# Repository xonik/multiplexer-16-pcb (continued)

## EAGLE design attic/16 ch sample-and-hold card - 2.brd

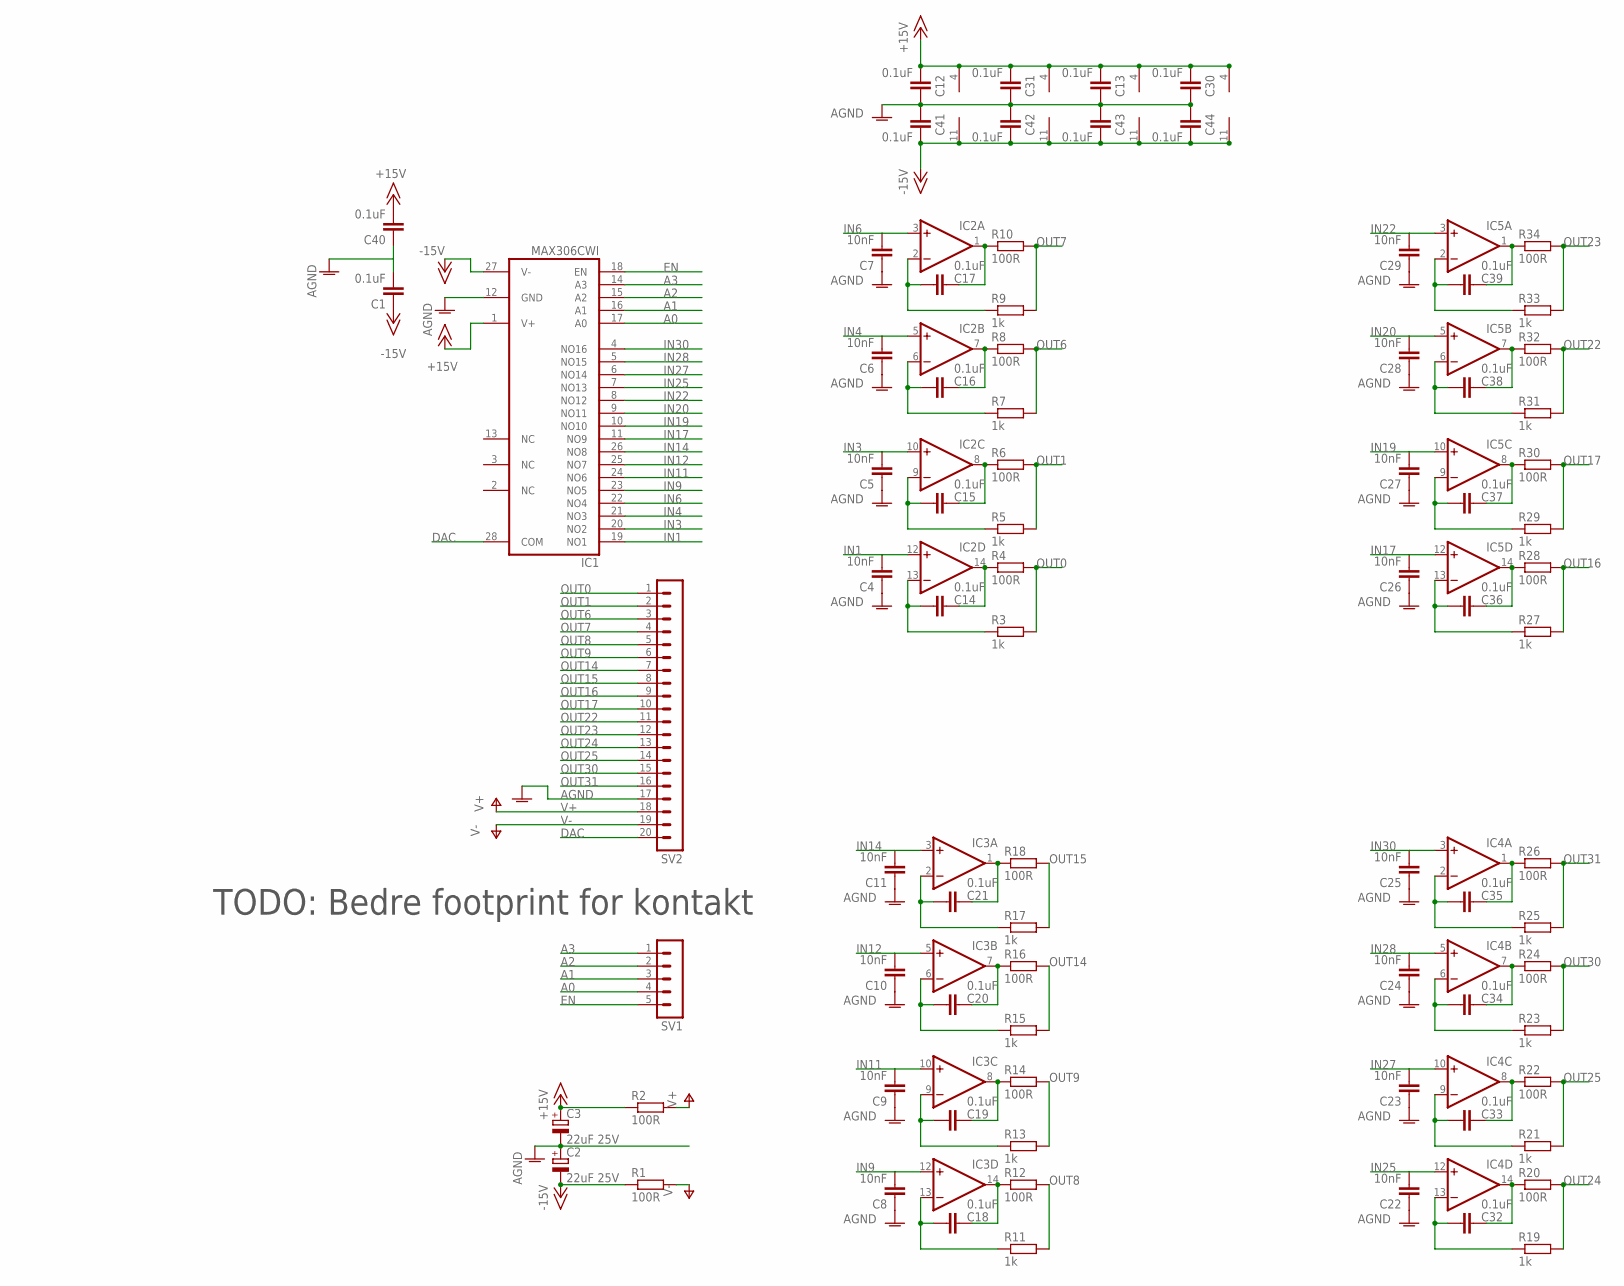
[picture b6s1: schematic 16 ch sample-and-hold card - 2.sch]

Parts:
C1, C12, C13, C14, C15, C16, C17, C18, C19, C20, C21, C30, C31, C32, C33, C34, C35, C36, C37, C38, C39, C40, C41, C42, C43, C44: 0.1uF; C0603
C2, C3: 22uF 25V; E2-5
C4, C5, C6, C7, C8, C9, C10, C11, C22, C23, C24, C25, C26, C27, C28, C29: 10nF; C1206
IC1: MAX306CWI; SO28L
IC2, IC3, IC4, IC5: TL074D; SO14
R1, R2: 100R; 0207/7
R3, R5, R7, R9, R11, R13, R15, R17, R19, R21, R23, R25, R27, R29, R31, R33: 1k; R0603
R4, R6, R8, R10, R12, R14, R16, R18, R20, R22, R24, R26, R28, R30, R32, R34: 100R; R0603
SV1: MA05-1
SV2: MA20-1

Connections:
+15V: C3.+, C12.1, C13.1, C30.1, C31.1, C40.2, IC1.1 (V+), IC2.4 (V+), IC3.4 (V+), IC4.4 (V+), IC5.4 (V+), R2.1
-15V: C1.1, C2.-, C41.2, C42.2, C43.2, C44.2, IC1.27 (V-), IC2.11 (V-), IC3.11 (V-), IC4.11 (V-), IC5.11 (V-), R1.1
A0: IC1.17 (A0), SV1.4
A1: IC1.16 (A1), SV1.3
A2: IC1.15 (A2), SV1.2
A3: IC1.14 (A3), SV1.1
AGND: C1.2, C2.+, C3.-, C4.1, C5.1, C6.1, C7.1, C8.1, C9.1, C10.1, C11.1, C12.2, C13.2, C22.1, C23.1, C24.1, C25.1, C26.1, C27.1, C28.1, C29.1, C30.2, C31.2, C40.1, C41.1, C42.1, C43.1, C44.1, IC1.12 (GND), SV2.17
DAC: IC1.28 (COM), SV2.20
EN: IC1.18 (EN), SV1.5
IN1: C4.2, IC1.19 (NO1), IC2.12 (+IN)
IN3: C5.2, IC1.20 (NO2), IC2.10 (+IN)
IN4: C6.2, IC1.21 (NO3), IC2.5 (+IN)
IN6: C7.2, IC1.22 (NO4), IC2.3 (+IN)
IN9: C8.2, IC1.23 (NO5), IC3.12 (+IN)
IN11: C9.2, IC1.24 (NO6), IC3.10 (+IN)
IN12: C10.2, IC1.25 (NO7), IC3.5 (+IN)
IN14: C11.2, IC1.26 (NO8), IC3.3 (+IN)
IN17: C26.2, IC1.11 (NO9), IC5.12 (+IN)
IN19: C27.2, IC1.10 (NO10), IC5.10 (+IN)
IN20: C28.2, IC1.9 (NO11), IC5.5 (+IN)
IN22: C29.2, IC1.8 (NO12), IC5.3 (+IN)
IN25: C22.2, IC1.7 (NO13), IC4.12 (+IN)
IN27: C23.2, IC1.6 (NO14), IC4.10 (+IN)
IN28: C24.2, IC1.5 (NO15), IC4.5 (+IN)
IN30: C25.2, IC1.4 (NO16), IC4.3 (+IN)
unnamed: C17.2, IC2.2 (-IN), R9.1
unnamed: C17.1, IC2.1 (OUT), R10.1
unnamed: C16.1, IC2.7 (OUT), R8.1
unnamed: C15.1, IC2.8 (OUT), R6.1
unnamed: C16.2, IC2.6 (-IN), R7.1
unnamed: C14.1, IC2.14 (OUT), R4.1
unnamed: C15.2, IC2.9 (-IN), R5.1
unnamed: C14.2, IC2.13 (-IN), R3.1
unnamed: C21.1, IC3.1 (OUT), R18.1
unnamed: C21.2, IC3.2 (-IN), R17.1
unnamed: C20.1, IC3.7 (OUT), R16.1
unnamed: C20.2, IC3.6 (-IN), R15.1
unnamed: C19.1, IC3.8 (OUT), R14.1
unnamed: C18.1, IC3.14 (OUT), R12.1
unnamed: C19.2, IC3.9 (-IN), R13.1
unnamed: C18.2, IC3.13 (-IN), R11.1
unnamed: C39.1, IC5.1 (OUT), R34.1
unnamed: C39.2, IC5.2 (-IN), R33.1
unnamed: C38.1, IC5.7 (OUT), R32.1
unnamed: C38.2, IC5.6 (-IN), R31.1
unnamed: C37.1, IC5.8 (OUT), R30.1
unnamed: C36.1, IC5.14 (OUT), R28.1
unnamed: C37.2, IC5.9 (-IN), R29.1
unnamed: C36.2, IC5.13 (-IN), R27.1
unnamed: C35.1, IC4.1 (OUT), R26.1
unnamed: C35.2, IC4.2 (-IN), R25.1
unnamed: C34.1, IC4.7 (OUT), R24.1
unnamed: C34.2, IC4.6 (-IN), R23.1
unnamed: C33.1, IC4.8 (OUT), R22.1
unnamed: C32.1, IC4.14 (OUT), R20.1
unnamed: C33.2, IC4.9 (-IN), R21.1
unnamed: C32.2, IC4.13 (-IN), R19.1
OUT0: R3.2, R4.2, SV2.1
OUT1: R5.2, R6.2, SV2.2
OUT6: R7.2, R8.2, SV2.3
OUT7: R9.2, R10.2, SV2.4
OUT8: R11.2, R12.2, SV2.5
OUT9: R13.2, R14.2, SV2.6
OUT14: R15.2, R16.2, SV2.7
OUT15: R17.2, R18.2, SV2.8
OUT16: R27.2, R28.2, SV2.9
OUT17: R29.2, R30.2, SV2.10
OUT22: R31.2, R32.2, SV2.11
OUT23: R33.2, R34.2, SV2.12
OUT24: R19.2, R20.2, SV2.13
OUT25: R21.2, R22.2, SV2.14
OUT30: R23.2, R24.2, SV2.15
OUT31: R25.2, R26.2, SV2.16
V+: R2.2, SV2.18
V-: R1.2, SV2.19

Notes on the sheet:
TODO: Bedre footprint for kontakt

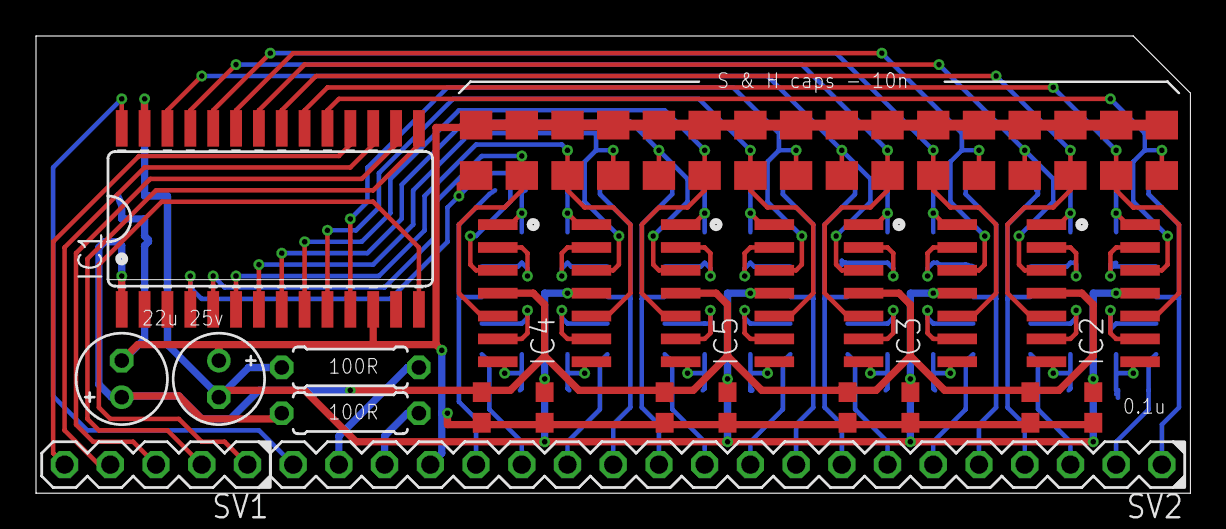
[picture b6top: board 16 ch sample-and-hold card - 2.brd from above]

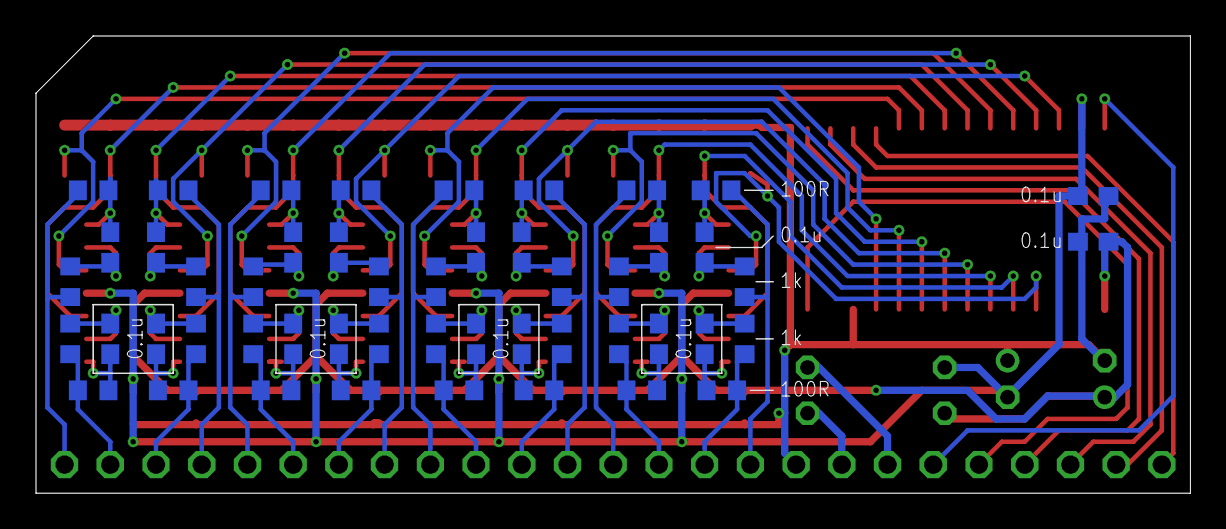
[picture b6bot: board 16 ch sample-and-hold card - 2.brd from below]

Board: 2 copper layers, 64.1 x 25.4 mm, 85 parts (50 on the bottom side), 75 nets.

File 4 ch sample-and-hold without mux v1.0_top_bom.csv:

Comment,Designator,Footprint,LCSC Part #
0.1uF,C31 C36 C37 C38 C39,C0603,C14663
1k,R27 R29 R31 R33,R0603,C21190
10nF,C26 C27 C28 C29,C0805,C1710
22uF 25V,C2 C3,CAPAE660X610N,C134761
100R,R1 R2,R0805,C17408
100R,R28 R30 R32 R34,R0603,C22775

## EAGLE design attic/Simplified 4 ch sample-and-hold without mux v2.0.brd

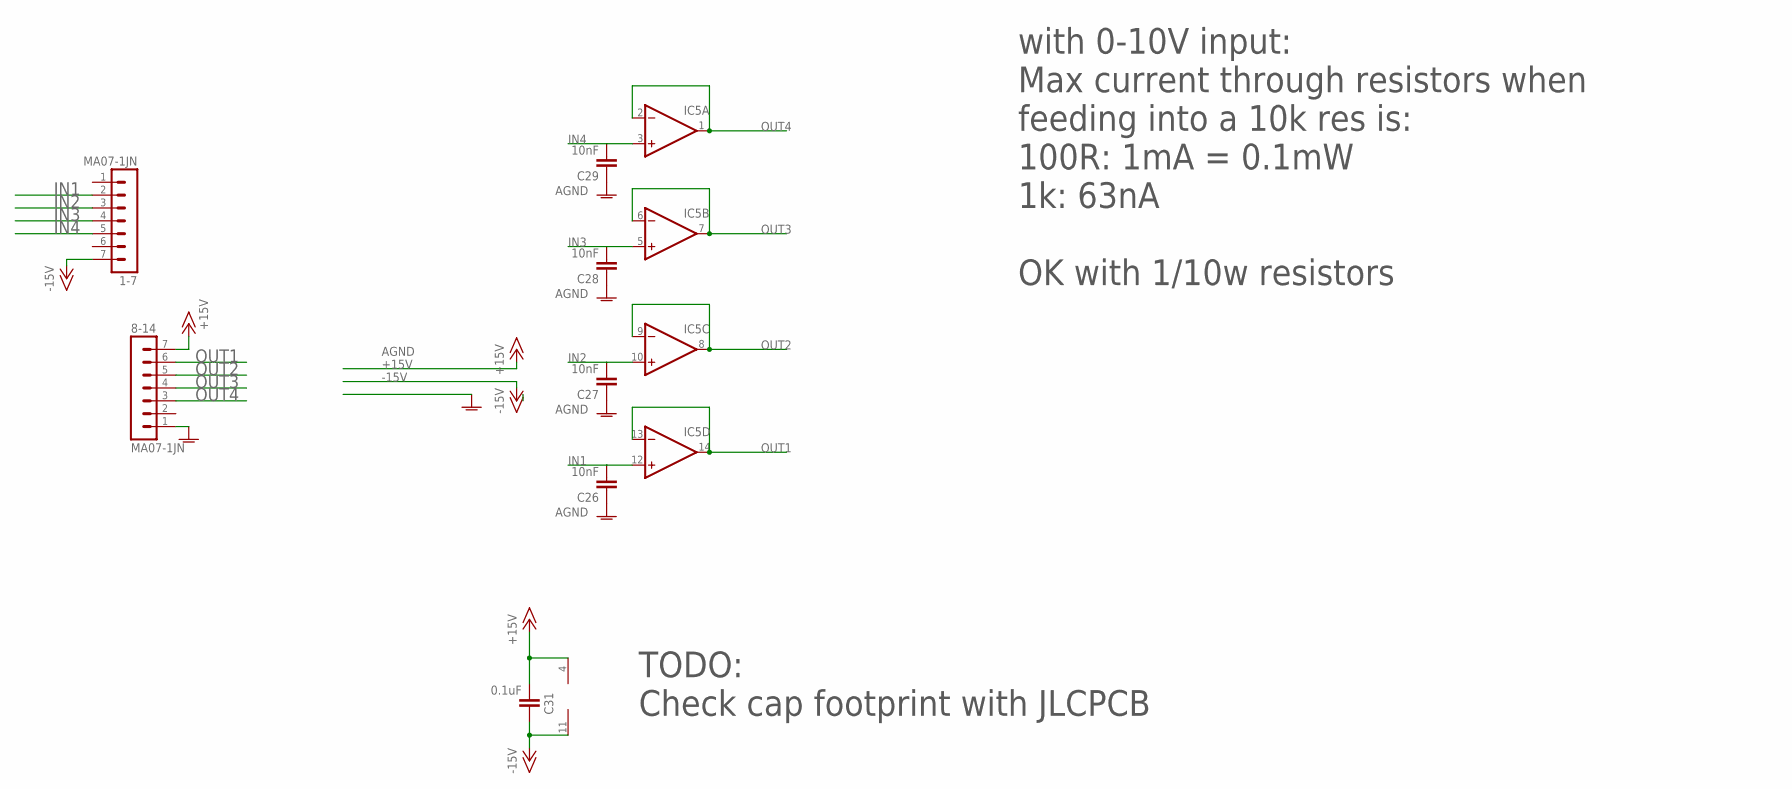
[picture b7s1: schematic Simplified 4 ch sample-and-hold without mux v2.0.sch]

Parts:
1-7, 8-14: MA07-1JN; MA07N-1J
C26, C27, C28, C29: 10nF; C0805
C31: 0.1uF; C0603
IC5: TL084CPWR; TSSOP14J

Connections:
+15V: 8-14.7, C31.1, IC5.4 (V+)
-15V: 1-7.7, C31.2, IC5.11 (V-)
AGND: 8-14.1, C26.1, C27.1, C28.1, C29.1
IN1: 1-7.2, C26.2, IC5.12 (+IN)
IN2: 1-7.3, C27.2, IC5.10 (+IN)
IN3: 1-7.4, C28.2, IC5.5 (+IN)
IN4: 1-7.5, C29.2, IC5.3 (+IN)
OUT1: 8-14.6, IC5.13 (-IN), IC5.14 (OUT)
OUT2: 8-14.5, IC5.8 (OUT), IC5.9 (-IN)
OUT3: 8-14.4, IC5.6 (-IN), IC5.7 (OUT)
OUT4: 8-14.3, IC5.1 (OUT), IC5.2 (-IN)

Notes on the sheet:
TODO: Check cap footprint with JLCPCB
with 0-10V input: Max current through resistors when feeding into a 10k res is: 100R: 1mA = 0.1mW 1k: 63nA OK with 1/10w resistors

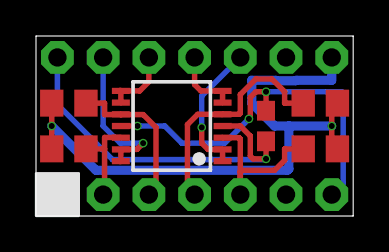
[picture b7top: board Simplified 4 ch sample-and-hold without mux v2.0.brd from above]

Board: 2 copper layers, 17.6 x 10.0 mm, 8 parts (0 on the bottom side), 11 nets.

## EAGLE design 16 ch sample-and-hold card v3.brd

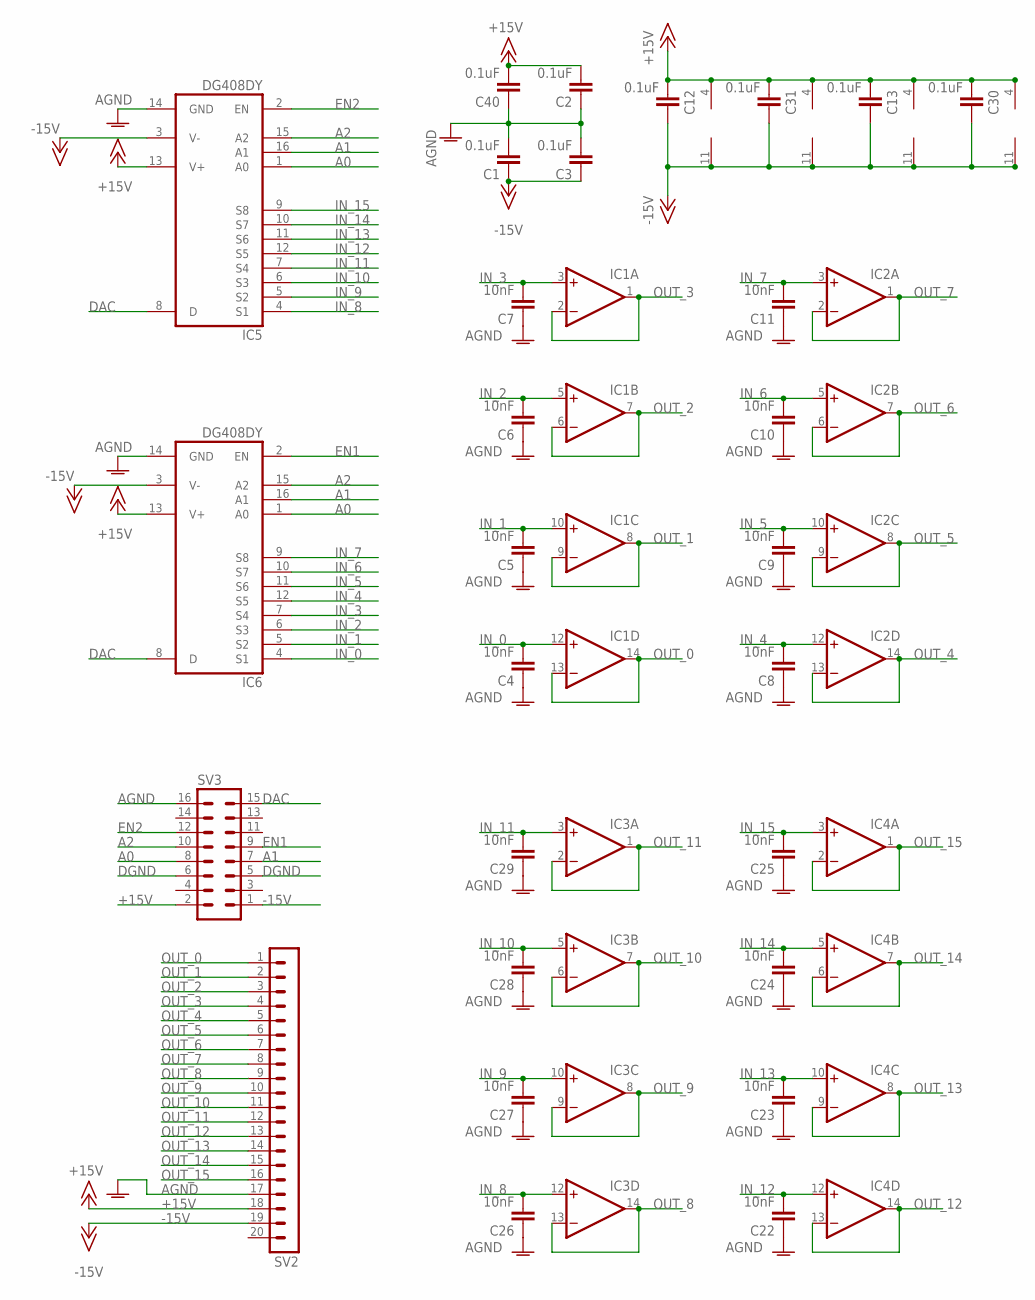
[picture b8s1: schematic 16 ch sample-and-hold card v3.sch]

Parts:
C1, C2, C3, C12, C13, C30, C31, C40: 0.1uF; C0603
C4, C5, C6, C7, C8, C9, C10, C11, C22, C23, C24, C25, C26, C27, C28, C29: 10nF; C1206
IC1, IC2, IC3, IC4: TL074D; SO14
IC5, IC6: DG408DY; SO16
SV2: MA20-1
SV3: MA08-2J

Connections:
+15V: C2.2, C12.1, C13.1, C30.1, C31.1, C40.2, IC1.4 (V+), IC2.4 (V+), IC3.4 (V+), IC4.4 (V+), IC5.13 (V+), IC6.13 (V+), SV2.18, SV3.2
-15V: C1.1, C3.1, C12.2, C13.2, C30.2, C31.2, IC1.11 (V-), IC2.11 (V-), IC3.11 (V-), IC4.11 (V-), IC5.3 (V-), IC6.3 (V-), SV2.19, SV3.1
A0: IC5.1 (A0), IC6.1 (A0), SV3.8
A1: IC5.16 (A1), IC6.16 (A1), SV3.7
A2: IC5.15 (A2), IC6.15 (A2), SV3.10
AGND: C1.2, C2.1, C3.2, C4.1, C5.1, C6.1, C7.1, C8.1, C9.1, C10.1, C11.1, C22.1, C23.1, C24.1, C25.1, C26.1, C27.1, C28.1, C29.1, C40.1, IC5.14 (GND), IC6.14 (GND), SV2.17, SV3.16
DAC: IC5.8 (D), IC6.8 (D), SV3.15
DGND: SV3.5, SV3.6
EN1: IC6.2 (EN), SV3.9
EN2: IC5.2 (EN), SV3.12
IN_0: C4.2, IC1.12 (+IN), IC6.4 (S1)
IN_1: C5.2, IC1.10 (+IN), IC6.5 (S2)
IN_2: C6.2, IC1.5 (+IN), IC6.6 (S3)
IN_3: C7.2, IC1.3 (+IN), IC6.7 (S4)
IN_4: C8.2, IC2.12 (+IN), IC6.12 (S5)
IN_5: C9.2, IC2.10 (+IN), IC6.11 (S6)
IN_6: C10.2, IC2.5 (+IN), IC6.10 (S7)
IN_7: C11.2, IC2.3 (+IN), IC6.9 (S8)
IN_8: C26.2, IC3.12 (+IN), IC5.4 (S1)
IN_9: C27.2, IC3.10 (+IN), IC5.5 (S2)
IN_10: C28.2, IC3.5 (+IN), IC5.6 (S3)
IN_11: C29.2, IC3.3 (+IN), IC5.7 (S4)
IN_12: C22.2, IC4.12 (+IN), IC5.12 (S5)
IN_13: C23.2, IC4.10 (+IN), IC5.11 (S6)
IN_14: C24.2, IC4.5 (+IN), IC5.10 (S7)
IN_15: C25.2, IC4.3 (+IN), IC5.9 (S8)
OUT_0: IC1.13 (-IN), IC1.14 (OUT), SV2.1
OUT_1: IC1.8 (OUT), IC1.9 (-IN), SV2.2
OUT_2: IC1.6 (-IN), IC1.7 (OUT), SV2.3
OUT_3: IC1.1 (OUT), IC1.2 (-IN), SV2.4
OUT_4: IC2.13 (-IN), IC2.14 (OUT), SV2.5
OUT_5: IC2.8 (OUT), IC2.9 (-IN), SV2.6
OUT_6: IC2.6 (-IN), IC2.7 (OUT), SV2.7
OUT_7: IC2.1 (OUT), IC2.2 (-IN), SV2.8
OUT_8: IC3.13 (-IN), IC3.14 (OUT), SV2.9
OUT_9: IC3.8 (OUT), IC3.9 (-IN), SV2.10
OUT_10: IC3.6 (-IN), IC3.7 (OUT), SV2.11
OUT_11: IC3.1 (OUT), IC3.2 (-IN), SV2.12
OUT_12: IC4.13 (-IN), IC4.14 (OUT), SV2.13
OUT_13: IC4.8 (OUT), IC4.9 (-IN), SV2.14
OUT_14: IC4.6 (-IN), IC4.7 (OUT), SV2.15
OUT_15: IC4.1 (OUT), IC4.2 (-IN), SV2.16

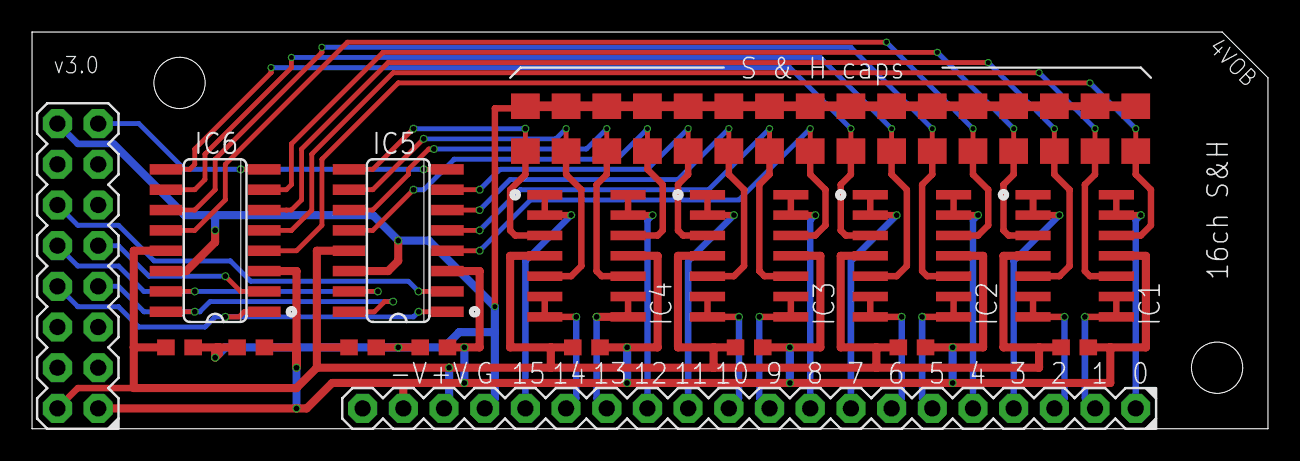
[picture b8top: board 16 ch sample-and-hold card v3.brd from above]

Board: 2 copper layers, 77.2 x 24.8 mm, 33 parts (1 on the bottom side), 42 nets.

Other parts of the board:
U$1: XONIK_LOGO_50

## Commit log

2018-07-23 Moved 16 ch sample and hold to separate repo
2018-07-23 Added logo and panelized
2018-08-02 Ordered combined sample and hold and vca
2020-02-17 Added 4 channel sample and hold without mux
2020-02-17 Going to replace cap
2020-02-17 Just missing logo
2020-02-17 Added logo
2020-02-18 Created parts list, cleaned up schematics
2020-02-22 Changed to logo-as-component
2020-03-02 Added bom and gerber
2020-03-02 Cleanup
2020-03-02 Something to ignore
2020-03-02 Making a simple buffered capacitor circuit, a minimal sample and hold thing that takes no more space than a normal 14p DIP
2020-03-03 Almost completed simplified 4ch s & h
2020-03-03 changed from 0.1uF to 330pF to align with Fat Controller circuit
2021-01-14 Fixed error in silk screen
2021-02-16 Created a new version of the 16ch sample and hold, better suited for my test controller
2021-02-17 Completed silk etc
2021-03-07 Added new version using 4051 MUX
2021-03-08 Added 5v reg for muxes directly on board
2021-03-09 Added selectable agnd/dgnd
2021-03-11 Added two wires for separate DAC channels to each mux on the SH board
2021-04-04 Added new version of s&h 4 using 0805 instead of 1206 caps
2022-04-08 moving
2024-06-11 Created 4ch buffer design element
2024-06-11 Working on 56 channel CV generator
2024-06-12 All cells for 56ch CV routed
2024-06-12 Mostly routed, needs DAC testing
2024-06-12 All routed, nothing tested
2024-06-12 Moved spare connectors to prevent misplacement of headers
2024-06-13 Added silk
2024-06-14 Split 22p into 15p and 7p
2024-06-14 Switched to 2p nude
2024-06-16 Fixes silk screen error, pin D0 was wrongly labled
2024-06-18 Switched to internal reference and buffering
2024-06-22 Fixed ground bug, finished tracing
2024-06-23 Changed dac footprint
2024-06-23 v1.0 ready for production
2024-06-25 Changed to 0.13mm traces to be on the safe side
2024-11-04 Added comment
2024-11-06 Error: Rear row is not connected!
2024-11-14 Created 4ch logic level shifter to use when DAC runs on 5v but is controlled by 3v3 Teensy. Also added comment about error in 56ch CV card
2024-11-20 Updated footprint
2024-11-20 Fixed errors in v1.0 and created v1.1 of 56ch - rear pins were not connected
